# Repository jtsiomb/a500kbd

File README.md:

Amiga 500 PS/2 keyboard controller
==================================

About
-----
This project is a PS/2 keyboard controller for the Amiga 500. It makes it
possible to connect and use an external PS/2 keyboard with the Amiga.

It's based on an AVR atmega168 microcontroller, which reads the PS/2 keyboard
and translates scancodes to the keyboard signals expected by the Amiga.

See pictures of the PS/2 controller in my Amiga: https://imgur.com/a/rhXS8

It has been reported that this works with the A600 too, by soldering directly
on the keyboard clock and data lines. I guess it might work with the A1200 as
well, so if anyone tries it please let me know.

Directory structure:

  * `hw` - hardware: kicad files and pdf schematics.
  * `fw` - firmware for the AVR microcontroller.

Project website: http://nuclear.mutantstargoat.com/hw/amiga/a500kbd

License
-------
Copyright (C) 2017 John Tsiombikas <nuclear@member.fsf.org>

You are free to use, reproduce, modify, redistribute any parts of this project,
provided you make any derivative work you release, freely available under the
same terms.

More specifically the hardware design is released under the Creative Commons
Attribution Share-Alike license (see `LICENSE.hw` for details), and the
software/firmware is released under the GNU General Public License v3, or later
(see `LICENSE.fw` for details).

Instructions
------------
Just construct the hardware, burn the firmware, drill appropriate holes, and
connect everything together. The board is designed to sit on top of the keyboard
connector pins on the Amiga motherboard, and provides a new set of pins for the
internal keyboard to be connected on the board. Two cables need to be connected
from the board to some hole on the Amiga case: one goes to the PS/2 connector,
and the other to the DPDT switch which selects between internal and external
keyboard (see: https://i.imgur.com/ovFDP2b.jpg).

The default key mapping (can only be changed by modifying the source code at the
moment), is as follows:

  * Caps lock key is mapped to control.
  * Left control key is mapped to left amiga key.
  * Right control key is mapped to right amiga key.
  * Scroll lock is mapped to caps lock.
  * F12 is mapped to "Help".

Also the scroll lock light on the external keyboard, mirrors the drive activity
LED on the amiga.

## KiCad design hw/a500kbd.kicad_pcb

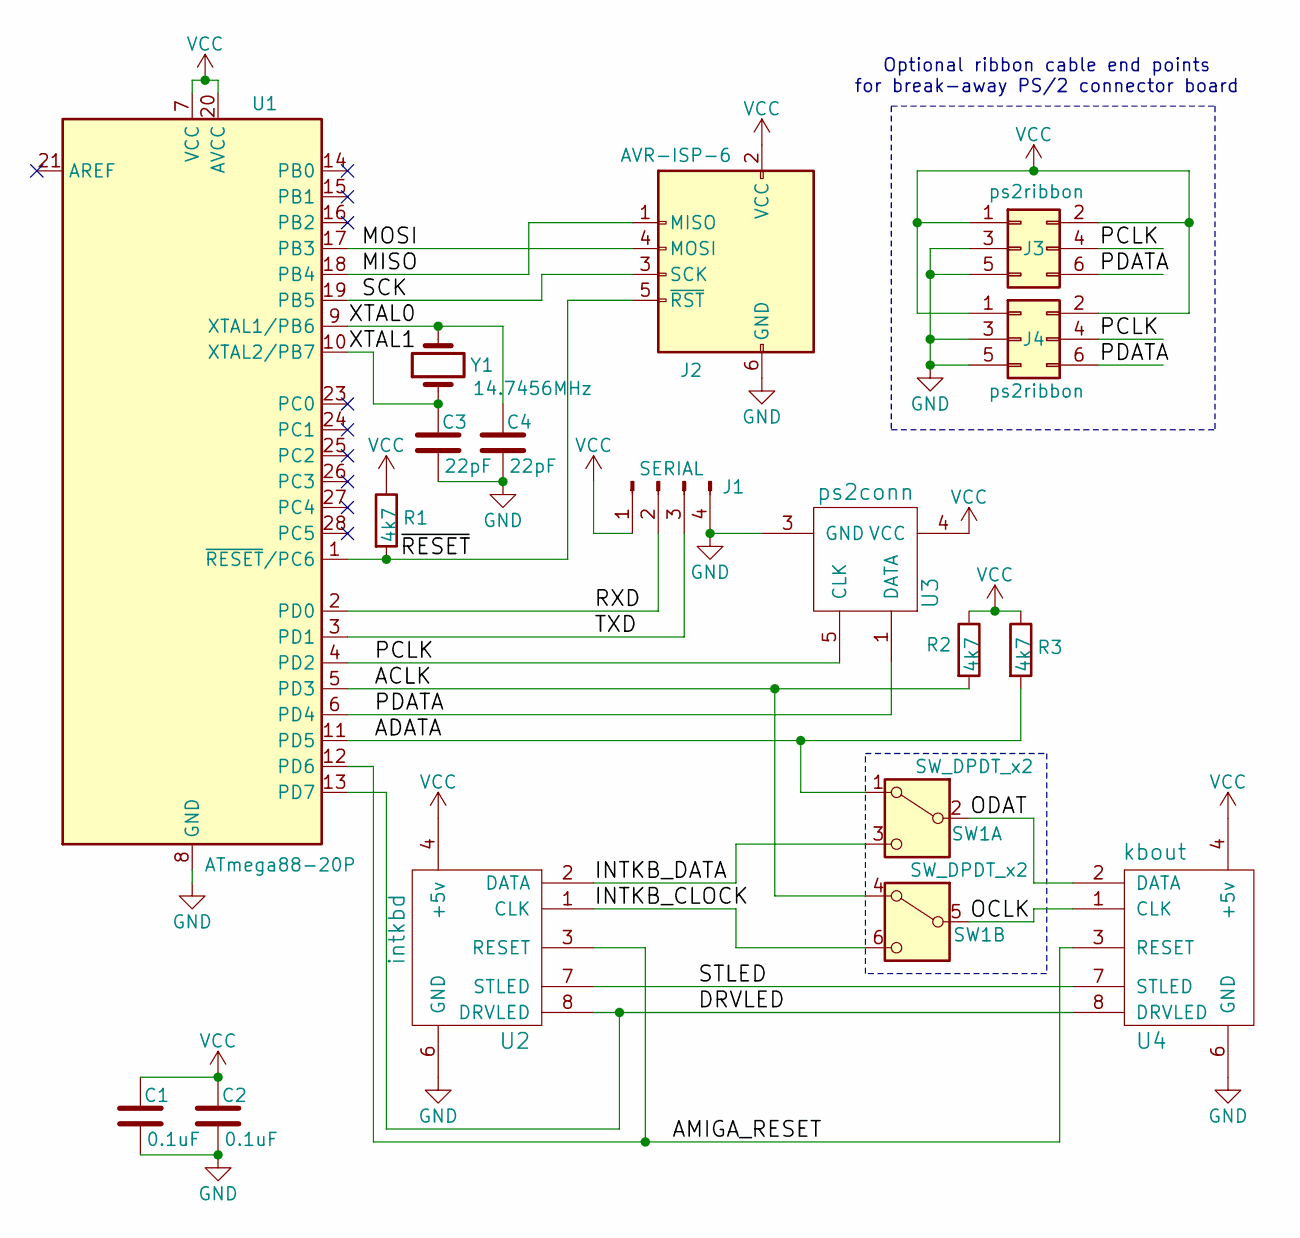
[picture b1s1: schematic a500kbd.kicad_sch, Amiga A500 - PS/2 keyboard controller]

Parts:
C1, C2: 0.1uF; C_Disc_D4.3mm_W1.9mm_P5.00mm
C3, C4: 22pF; C_Disc_D3.0mm_W2.0mm_P2.50mm
J1: SERIAL; PinHeader_1x04_P2.54mm_Horizontal
J2: AVR-ISP-6; IDC-Header_2x03_P2.54mm_Vertical
J3, J4: ps2ribbon; IDC-Header_2x03_P2.54mm_Vertical
R1, R2, R3: 4k7; R_Axial_DIN0207_L6.3mm_D2.5mm_P10.16mm_Horizontal
SW1: SW_DPDT_x2; kbswitch
U1: ATmega88-20P; DIP-28_W7.62mm
U2: intkbd; PinHeader_1x08_P2.54mm_Vertical
U3: ps2conn; minidin6
U4: kbout; PinSocket_1x08_P2.54mm_Vertical
Y1: 14.7456MHz; Crystal_HC49-U_Vertical

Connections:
/ACLK: R2.2, SW1.4 (A), U1.5 (PD3)
/ADATA: R3.2, SW1.1 (A), U1.11 (PD5)
/AMIGA_RESET: U1.12 (PD6), U2.3 (RESET), U4.3 (RESET)
/DRVLED: U1.13 (PD7), U2.8 (DRVLED), U4.8 (DRVLED)
/INTKB_CLOCK: SW1.6 (C), U2.1 (CLK)
/INTKB_DATA: SW1.3 (C), U2.2 (DATA)
/MISO: J2.1 (MISO), U1.18 (PB4)
/MOSI: J2.4 (MOSI), U1.17 (PB3)
/OCLK: SW1.5 (B), U4.1 (CLK)
/ODAT: SW1.2 (B), U4.2 (DATA)
/PCLK: J3.4, J4.4, U1.4 (PD2), U3.5 (CLK)
/PDATA: J3.6, J4.6, U1.6 (PD4), U3.1 (DATA)
/RXD: J1.2, U1.2 (PD0)
/SCK: J2.3 (SCK), U1.19 (PB5)
/STLED: U2.7 (STLED), U4.7 (STLED)
/TXD: J1.3, U1.3 (PD1)
/XTAL0: C4.1, U1.9 (XTAL1/PB6), Y1.2
/XTAL1: C3.1, U1.10 (XTAL2/PB7), Y1.1
/~RESET: J2.5 (~RST), R1.2, U1.1 (~RESET/PC6)
GND: C1.2, C2.2, C3.2, C4.2, J1.4, J2.6 (GND), J3.3, J3.5, J4.3, J4.5, U1.8 (GND), U1.22 (GND), U2.6 (GND), U3.3 (GND), U4.6 (GND)
VCC: C1.1, C2.1, J1.1, J2.2 (VCC), J3.1, J3.2, J4.1, J4.2, R1.1, R2.1, R3.1, U1.7 (VCC), U1.20 (AVCC), U2.4 (+5v), U3.4 (VCC), U4.4 (+5v)

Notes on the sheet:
Optional ribbon cable end points for break-away PS/2 connector board

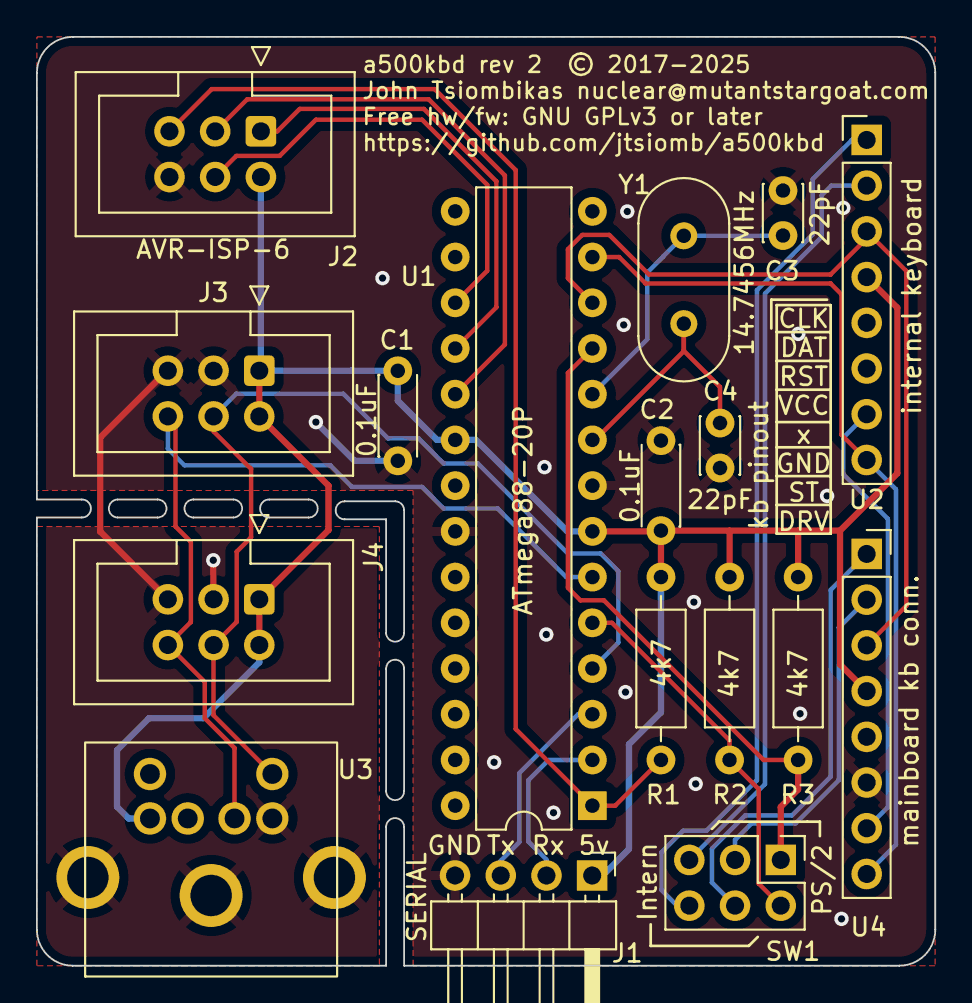
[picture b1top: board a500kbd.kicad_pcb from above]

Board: 2 copper layers, 49.9 x 51.6 mm, 17 parts (0 on the bottom side), 21 nets.

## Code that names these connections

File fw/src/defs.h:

#ifndef DEFS_H_
#define DEFS_H_

#include <avr/io.h>

/* pin assignments:
 * D2	PS/2 clock (INT0)
 * D3	amikbd clock (INT1)
 * D4	PS/2 data
 * D5	amikbd data
 * D6	amiga reset
 * D7	amiga drvled in
 */

#define PCLK	2
#define ACLK	3
#define PDATA	4
#define ADATA	5
#define ARST	6
#define ADRVLED	7

#define PCLK_BIT	(1 << PCLK)
#define ACLK_BIT	(1 << ACLK)
#define PDATA_BIT	(1 << PDATA)
#define ADATA_BIT	(1 << ADATA)
#define ARST_BIT	(1 << ARST)
#define ADRVLED_BIT	(1 << ADRVLED)

#endif	/* DEFS_H_ */

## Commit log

2017-10-18 amiga 500 ps/2 keyboard controller initial commit
2017-12-22 updated readme with A600 info
2017-12-23 Trying to solve the spurious keystrokes after reset problem.
2017-12-24 Fix spurious keystrokes on reset. Increase ps2 buffer to 32 for multiple keypresses
2017-12-24 minor coding style fixes
2017-12-25 Add hook for F11 press. Add layout switching with F11. Status shown with numlock LED. Alternative layout is Colemak.
2018-12-21 fixed project page url in readme
2022-06-30 kicad project update
2025-05-21 build for atmega88, and attempt to improve reset reliability
2025-05-21 PCB design
2025-05-22 fix pcb cutouts and minor re-routing of a signal
2025-05-23 fixed (swapped) the placement of the amiga keyboard connectors
2025-05-24 fixed mirrored ps2 connector in schematic
2025-06-20 fixed pcb, ps/2 connector facing the wrong way
2025-07-04 makefile options

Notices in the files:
hw/a500kbd.kicad_pcb:
a500kbd rev 2  © 2017-2025
Free hw/fw: GNU GPLv3 or later
hw/a500kbd.kicad_sch:
Creative Commons Attribution Share-Alike (CC BY-SA)
Copyright (C) 2017-2025 John Tsiombikas
